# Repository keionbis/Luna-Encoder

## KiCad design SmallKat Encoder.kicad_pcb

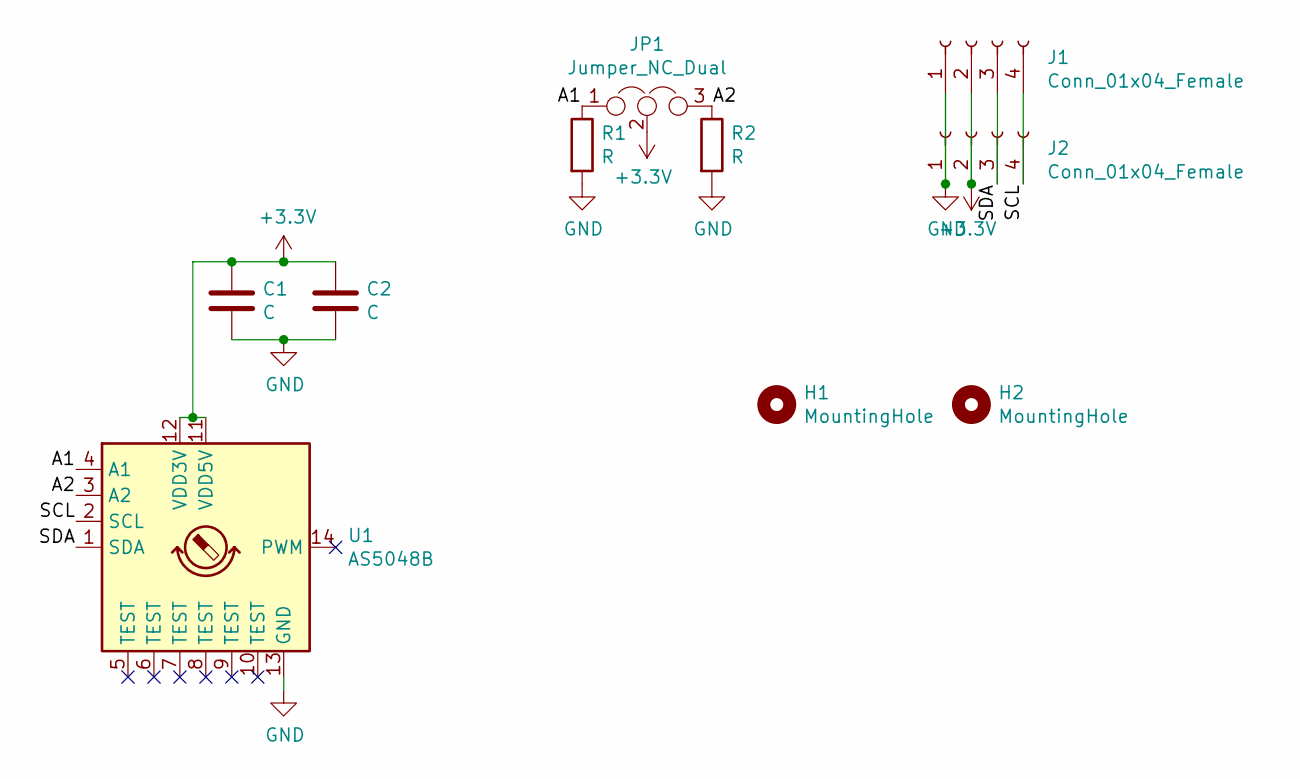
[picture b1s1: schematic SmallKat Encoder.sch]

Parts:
C1, C2: C; C_0402_1005Metric
H1, H2: MountingHole; MountingHole_3.2mm_M3
J1, J2: Conn_01x04_Female; JST_SH_SM04B-SRSS-TB_1x04-1MP_P1.00mm_Horizontal
JP1: Jumper_NC_Dual; SolderJumper-3_P1.3mm_Bridged12_Pad1.0x1.5mm
R1, R2: R; R_0402_1005Metric
U1: AS5048B; TSSOP-14_4.4x5mm_P0.65mm

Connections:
+3V3: C1.1, C2.1, J1.2, J2.2, JP1.2, U1.11 (VDD5V), U1.12 (VDD3V)
/A1: JP1.1, R1.1, U1.4 (A1)
/A2: JP1.3, R2.1, U1.3 (A2)
/SCL: J1.4, J2.4, U1.2 (SCL)
/SDA: J1.3, J2.3, U1.1 (SDA)
GND: C1.2, C2.2, J1.1, J2.1, R1.2, R2.2, U1.13 (GND)

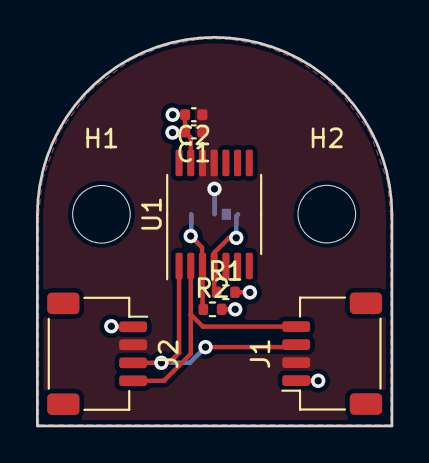
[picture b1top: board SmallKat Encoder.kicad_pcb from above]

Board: 2 copper layers, 19.7 x 21.6 mm, 10 parts (1 on the bottom side), 6 nets.

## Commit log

2021-02-03 Added step
